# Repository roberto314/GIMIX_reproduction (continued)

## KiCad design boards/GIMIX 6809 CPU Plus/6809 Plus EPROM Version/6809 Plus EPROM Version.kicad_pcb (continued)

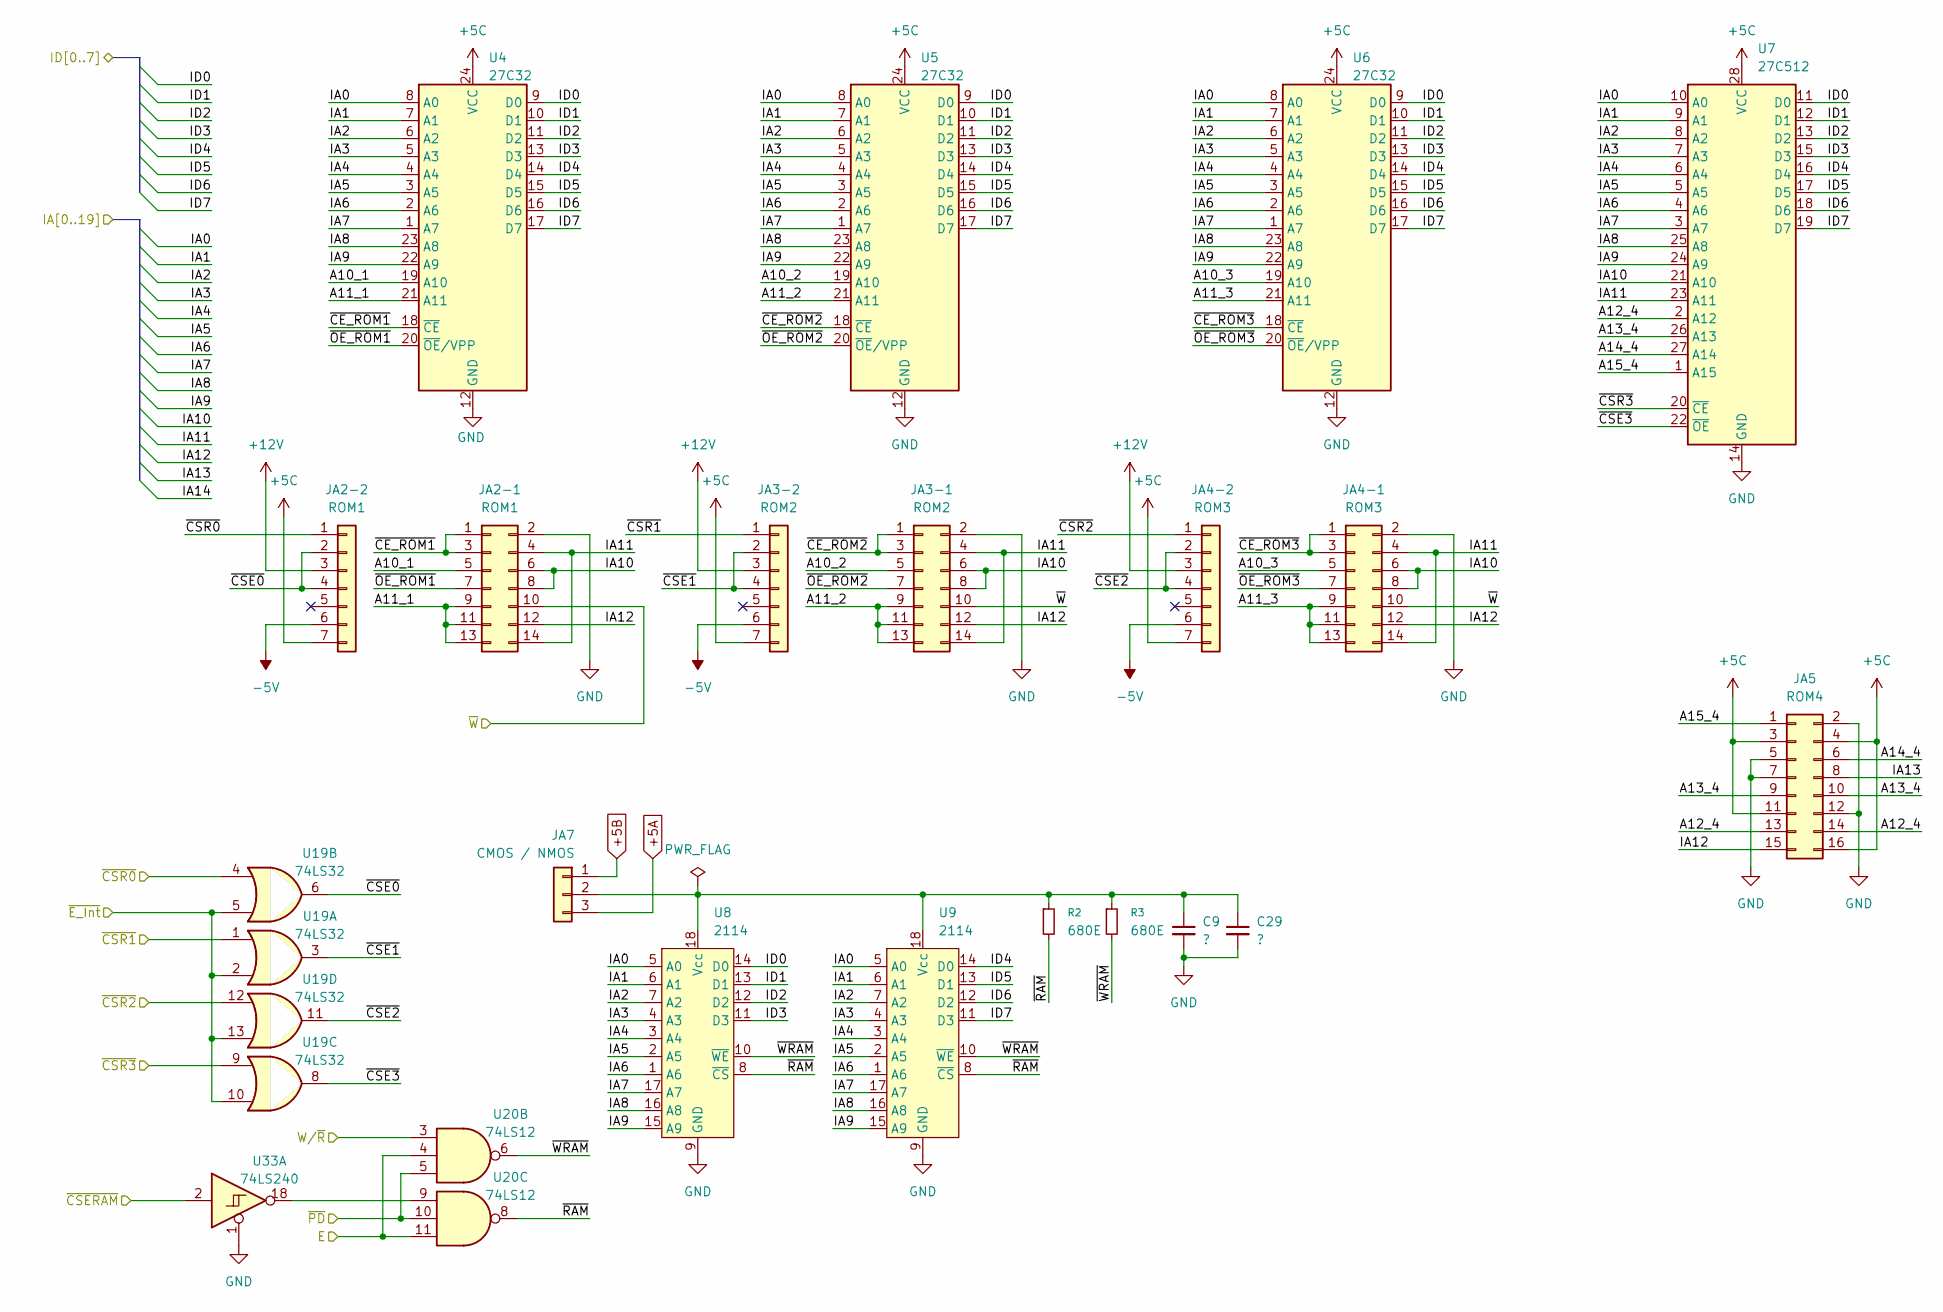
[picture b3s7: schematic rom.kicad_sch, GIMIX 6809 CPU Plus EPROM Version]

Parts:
C9, C29: ?; C_Disc_D3.8mm_W2.6mm_P2.50mm
JA2-1: ROM1; PinHeader_2x07_P2.54mm_Vertical
JA2-2: ROM1; PinHeader_1x07_P2.54mm_Vertical
JA3-1: ROM2; PinHeader_2x07_P2.54mm_Vertical
JA3-2: ROM2; PinHeader_1x07_P2.54mm_Vertical
JA4-1: ROM3; PinHeader_2x07_P2.54mm_Vertical
JA4-2: ROM3; PinHeader_1x07_P2.54mm_Vertical
JA5: ROM4; PinHeader_2x08_P2.54mm_Vertical
JA7: CMOS / NMOS; PinHeader_1x03_P2.54mm_Vertical
R2, R3: 680E; R_Axial_DIN0207_L6.3mm_D2.5mm_P10.16mm_Horizontal
U4, U5, U6: 27C32; DIP-24_W15.24mm
U7: 27C512; DIP-28_W15.24mm
U8, U9: 2114; DIP-18_W7.62mm
U19: 74LS32; DIP-14_W7.62mm
U20: 74LS12; DIP-14_W7.62mm
U33: 74LS240; DIP-20_W7.62mm

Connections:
+5A: JA7.3; also elsewhere on the board
+5B: JA7.1; also elsewhere on the board
+5C: JA2-2.7, JA3-2.7, JA4-2.7, JA5.3, JA5.4, JA5.11, JA5.16, U4.24 (VCC), U5.24 (VCC), U6.24 (VCC), U7.28 (VCC); also elsewhere on the board
+12V: JA2-2.3, JA3-2.3, JA4-2.3; also elsewhere on the board
-5V: JA2-2.6, JA3-2.6, JA4-2.6; also elsewhere on the board
/E: U20.4, U20.11; also elsewhere on the board
/IA0: U4.8 (A0), U5.8 (A0), U6.8 (A0), U7.10 (A0), U8.5 (A0), U9.5 (A0); also elsewhere on the board
/IA1: U4.7 (A1), U5.7 (A1), U6.7 (A1), U7.9 (A1), U8.6 (A1), U9.6 (A1); also elsewhere on the board
/IA2: U4.6 (A2), U5.6 (A2), U6.6 (A2), U7.8 (A2), U8.7 (A2), U9.7 (A2); also elsewhere on the board
/IA3: U4.5 (A3), U5.5 (A3), U6.5 (A3), U7.7 (A3), U8.4 (A3), U9.4 (A3); also elsewhere on the board
/IA4: U4.4 (A4), U5.4 (A4), U6.4 (A4), U7.6 (A4), U8.3 (A4), U9.3 (A4); also elsewhere on the board
/IA5: U4.3 (A5), U5.3 (A5), U6.3 (A5), U7.5 (A5), U8.2 (A5), U9.2 (A5); also elsewhere on the board
/IA6: U4.2 (A6), U5.2 (A6), U6.2 (A6), U7.4 (A6), U8.1 (A6), U9.1 (A6); also elsewhere on the board
/IA7: U4.1 (A7), U5.1 (A7), U6.1 (A7), U7.3 (A7), U8.17 (A7), U9.17 (A7); also elsewhere on the board
/IA8: U4.23 (A8), U5.23 (A8), U6.23 (A8), U7.25 (A8), U8.16 (A8), U9.16 (A8); also elsewhere on the board
/IA9: U4.22 (A9), U5.22 (A9), U6.22 (A9), U7.24 (A9), U8.15 (A9), U9.15 (A9); also elsewhere on the board
/IA10: JA2-1.6, JA2-1.8, JA3-1.6, JA3-1.8, JA4-1.6, JA4-1.8, U7.21 (A10); also elsewhere on the board
/IA11: JA2-1.4, JA2-1.14, JA3-1.4, JA3-1.14, JA4-1.4, JA4-1.14, U7.23 (A11); also elsewhere on the board
/IA12: JA2-1.12, JA3-1.12, JA4-1.12, JA5.15; also elsewhere on the board
/IA13: JA5.8; also elsewhere on the board
/ID0: U4.9 (D0), U5.9 (D0), U6.9 (D0), U7.11 (D0), U8.14 (D0); also elsewhere on the board
/ID1: U4.10 (D1), U5.10 (D1), U6.10 (D1), U7.12 (D1), U8.13 (D1); also elsewhere on the board
/ID2: U4.11 (D2), U5.11 (D2), U6.11 (D2), U7.13 (D2), U8.12 (D2); also elsewhere on the board
/ID3: U4.13 (D3), U5.13 (D3), U6.13 (D3), U7.15 (D3), U8.11 (D3); also elsewhere on the board
/ID4: U4.14 (D4), U5.14 (D4), U6.14 (D4), U7.16 (D4), U9.14 (D0); also elsewhere on the board
/ID5: U4.15 (D5), U5.15 (D5), U6.15 (D5), U7.17 (D5), U9.13 (D1); also elsewhere on the board
/ID6: U4.16 (D6), U5.16 (D6), U6.16 (D6), U7.18 (D6), U9.12 (D2); also elsewhere on the board
/ID7: U4.17 (D7), U5.17 (D7), U6.17 (D7), U7.19 (D7), U9.11 (D3); also elsewhere on the board
/ROM/A10_1: JA2-1.5, U4.19 (A10)
/ROM/A10_2: JA3-1.5, U5.19 (A10)
/ROM/A10_3: JA4-1.5, U6.19 (A10)
/ROM/A11_1: JA2-1.9, JA2-1.11, JA2-1.13, U4.21 (A11)
/ROM/A11_2: JA3-1.9, JA3-1.11, JA3-1.13, U5.21 (A11)
/ROM/A11_3: JA4-1.9, JA4-1.11, JA4-1.13, U6.21 (A11)
/ROM/A12_4: JA5.13, JA5.14, U7.2 (A12)
/ROM/A13_4: JA5.9, JA5.10, U7.26 (A13)
/ROM/A14_4: JA5.6, U7.27 (A14)
/ROM/A15_4: JA5.1, U7.1 (A15)
/ROM/~CE_ROM1: JA2-1.1, JA2-1.3, U4.18 (~CE)
/ROM/~CE_ROM2: JA3-1.1, JA3-1.3, U5.18 (~CE)
/ROM/~CE_ROM3: JA4-1.1, JA4-1.3, U6.18 (~CE)
/ROM/~CSE0: JA2-2.2, JA2-2.4, U19.6
/ROM/~CSE1: JA3-2.2, JA3-2.4, U19.3
/ROM/~CSE2: JA4-2.2, JA4-2.4, U19.11
/ROM/~CSE3: U7.22 (~OE), U19.8
/ROM/~OE_ROM1: JA2-1.7, U4.20 (~OE/VPP)
/ROM/~OE_ROM2: JA3-1.7, U5.20 (~OE/VPP)
/ROM/~OE_ROM3: JA4-1.7, U6.20 (~OE/VPP)
/ROM/~RAM: R2.2, U8.8 (~CS), U9.8 (~CS), U20.8
/ROM/~WRAM: R3.2, U8.10 (~WE), U9.10 (~WE), U20.6
/W/~R: U20.3; also elsewhere on the board
/~CSERAM: U33.2; also elsewhere on the board
/~CSR0: JA2-2.1, U19.4; also elsewhere on the board
/~CSR1: JA3-2.1, U19.1; also elsewhere on the board
/~CSR2: JA4-2.1, U19.12; also elsewhere on the board
/~CSR3: U7.20 (~CE), U19.9; also elsewhere on the board
/~E_Int: U19.2, U19.5, U19.10, U19.13; also elsewhere on the board
/~PD: U20.5, U20.10; also elsewhere on the board
/~W: JA2-1.10, JA3-1.10, JA4-1.10; also elsewhere on the board
GND: C9.2, C29.2, JA2-1.2, JA3-1.2, JA4-1.2, JA5.2, JA5.5, JA5.7, JA5.12, U4.12 (GND), U5.12 (GND), U6.12 (GND), U7.14 (GND), U8.9 (GND), U9.9 (GND), U33.1; also elsewhere on the board
unnamed: C9.1, C29.1, JA7.2, R2.1, R3.1, U8.18 (Vcc), U9.18 (Vcc)
unnamed: U20.9, U33.18

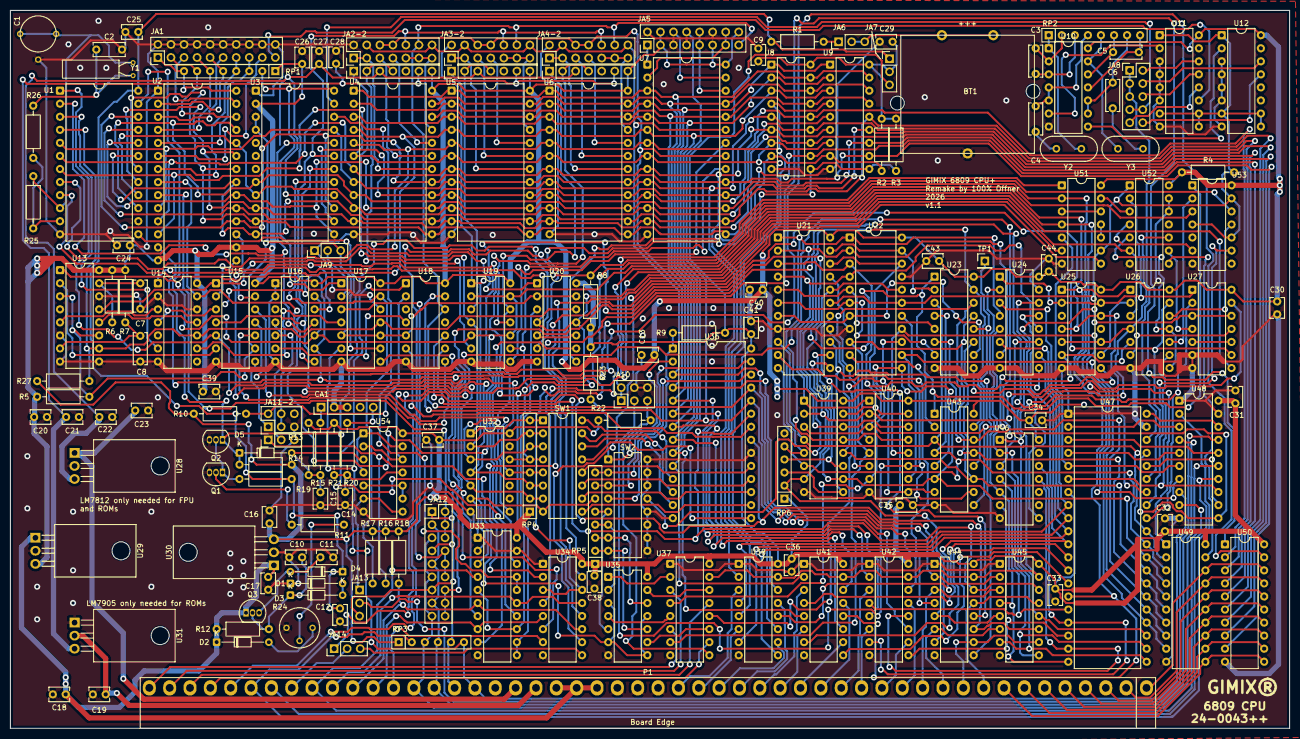
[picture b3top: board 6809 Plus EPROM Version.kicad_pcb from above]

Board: 2 copper layers, 248.9 x 139.7 mm, 167 parts (0 on the bottom side), 294 nets.

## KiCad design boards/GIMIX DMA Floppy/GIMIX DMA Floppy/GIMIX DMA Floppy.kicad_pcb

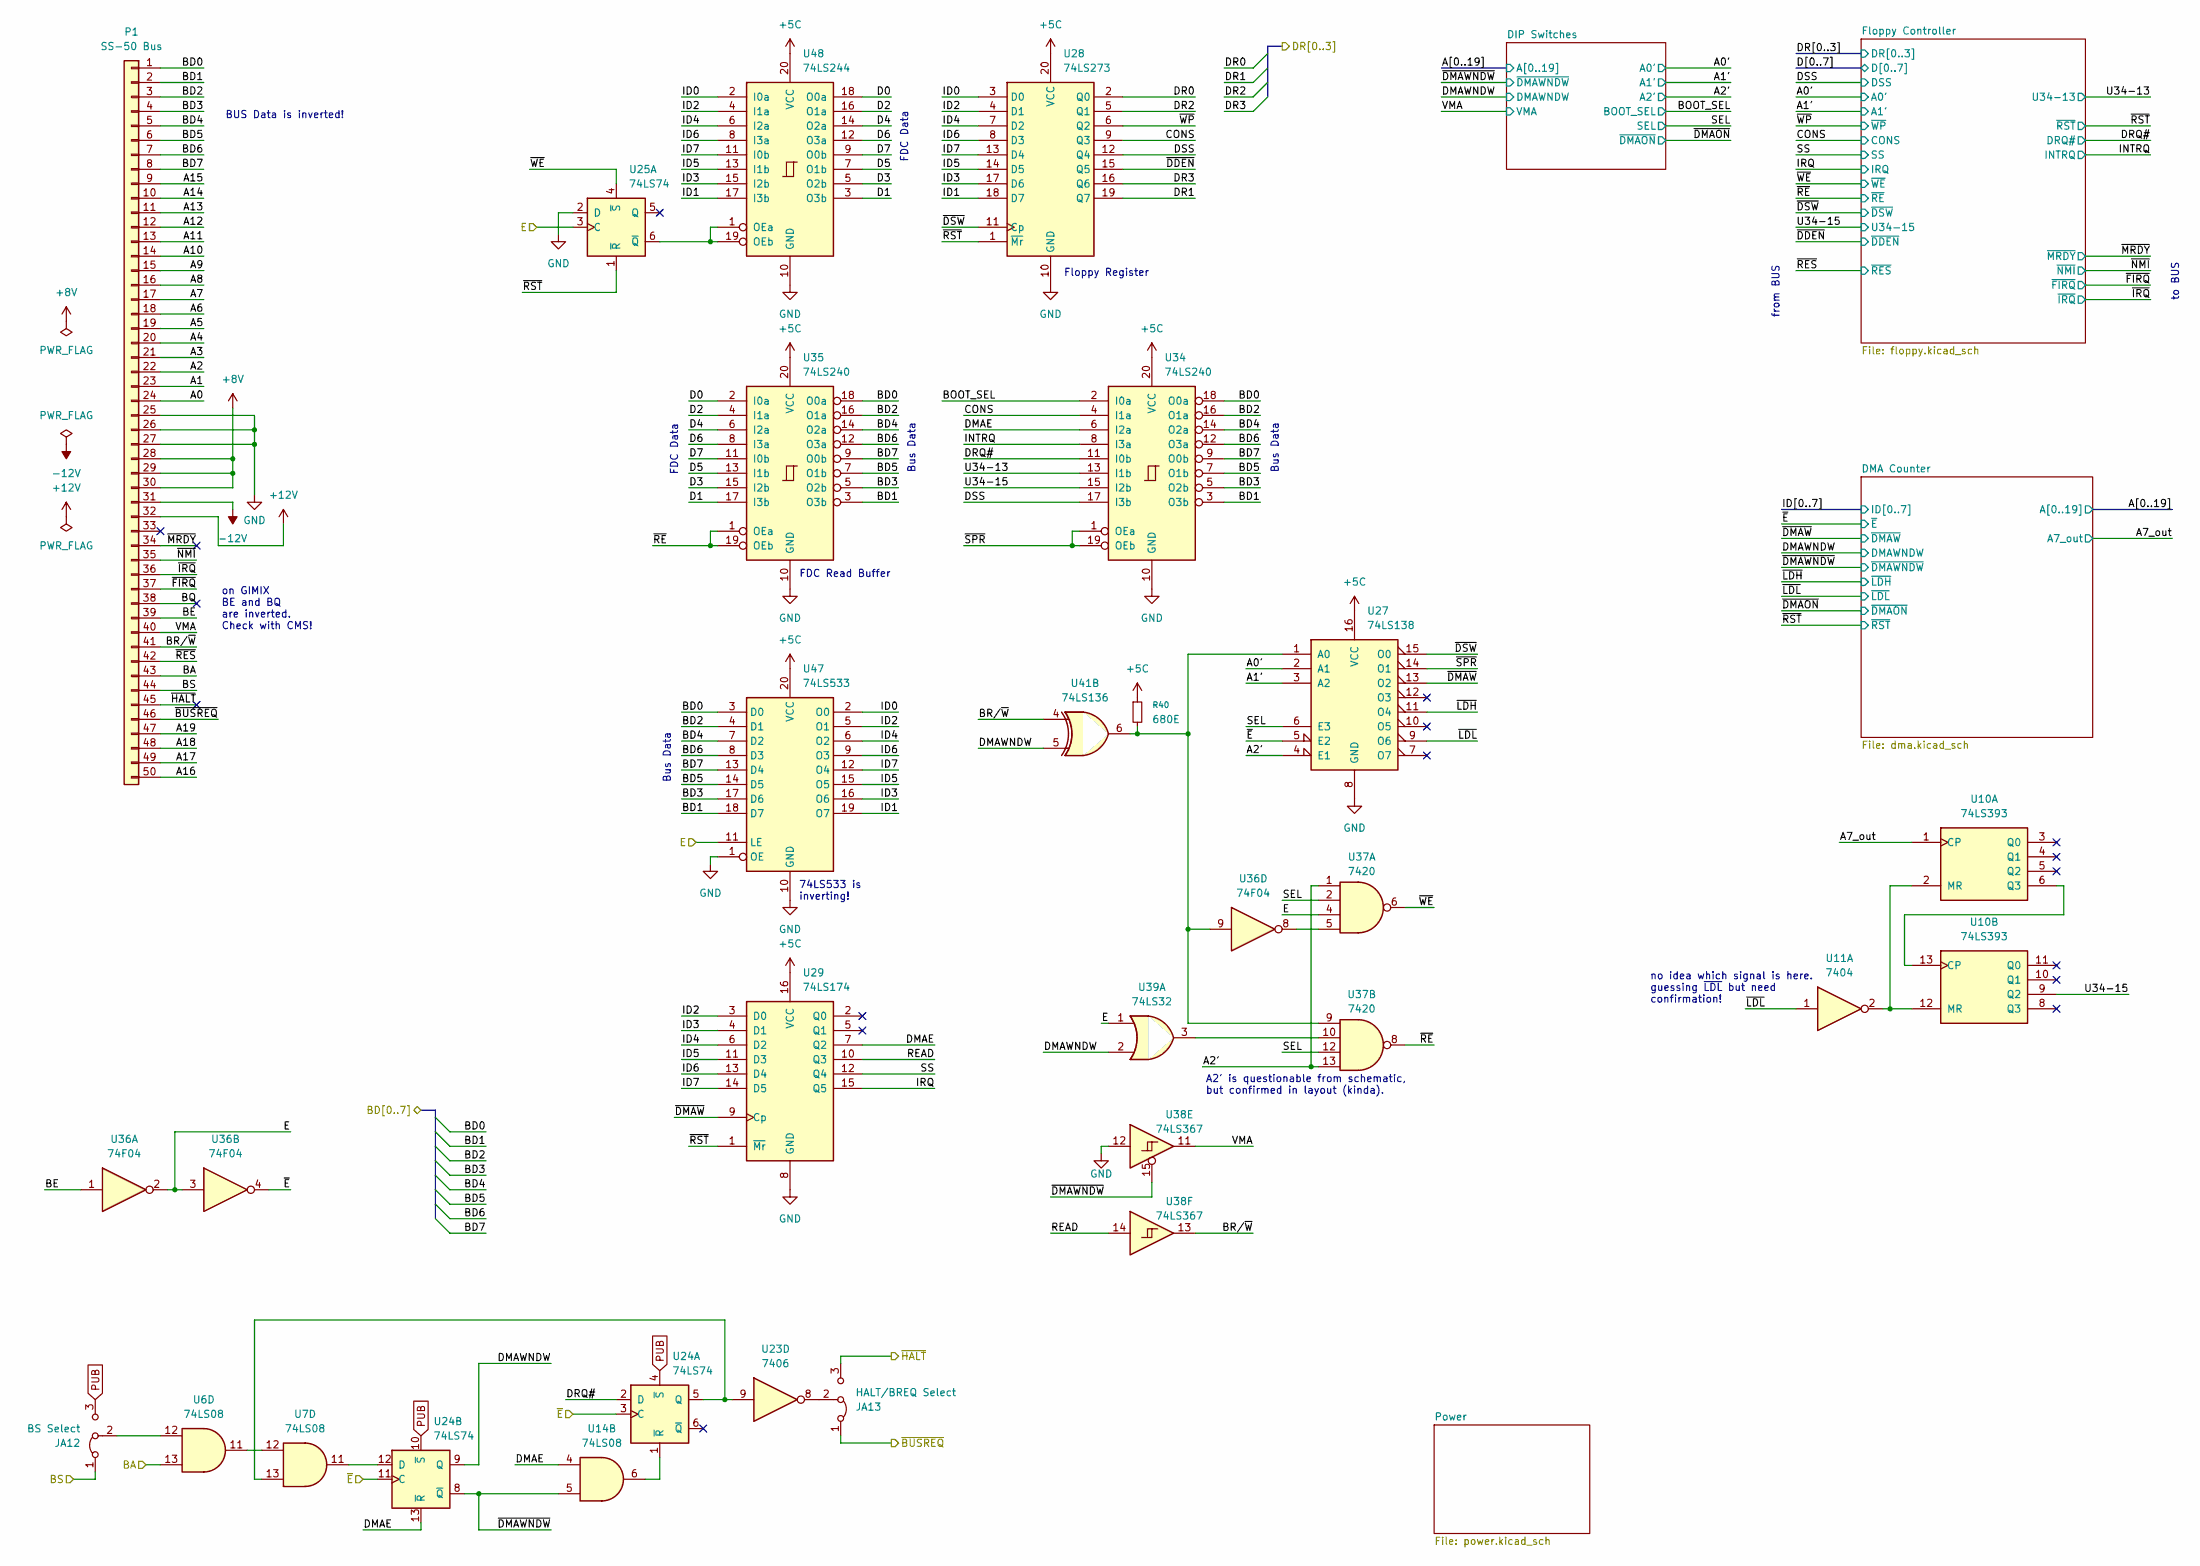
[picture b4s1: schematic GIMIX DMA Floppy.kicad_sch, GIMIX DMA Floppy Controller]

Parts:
JA12: BS Select; PinHeader_1x03_P2.54mm_Vertical
JA13: HALT/BREQ Select; PinHeader_1x03_P2.54mm_Vertical
P1: SS-50 Bus; SS-50_new
R40: 680E; R_Axial_DIN0207_L6.3mm_D2.5mm_P10.16mm_Horizontal
U6, U7, U14: 74LS08; DIP-14_W7.62mm
U10: 74LS393; DIP-14_W7.62mm
U11: 7404; DIP-14_W7.62mm
U23: 7406; DIP-14_W7.62mm
U24, U25: 74LS74; DIP-14_W7.62mm
U27: 74LS138; DIP-16_W7.62mm
U28: 74LS273; DIP-20_W7.62mm
U29: 74LS174; DIP-16_W7.62mm
U34, U35: 74LS240; DIP-20_W7.62mm
U36: 74F04; DIP-14_W7.62mm
U37: 7420; DIP-14_W7.62mm
U38: 74LS367; DIP-16_W7.62mm
U39: 74LS32; DIP-14_W7.62mm
U41: 74LS136; DIP-14_W7.62mm
U47: 74LS533; DIP-20_W7.62mm
U48: 74LS244; DIP-20_W7.62mm

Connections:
+5C: R40.1, U27.16 (VCC), U28.20 (VCC), U29.16 (VCC), U34.20 (VCC), U35.20 (VCC), U47.20 (VCC), U48.20 (VCC); also elsewhere on the board
+8V: P1.28, P1.29, P1.30; also elsewhere on the board
+12V: P1.32
-12V: P1.31
/A0: P1.24; also elsewhere on the board
/A0': U27.2 (A1); also elsewhere on the board
/A1: P1.23; also elsewhere on the board
/A1': U27.3 (A2); also elsewhere on the board
/A2: P1.22; also elsewhere on the board
/A2': U27.4 (E1), U37.1, U37.13; also elsewhere on the board
/A3: P1.21; also elsewhere on the board
/A4: P1.20; also elsewhere on the board
/A5: P1.19; also elsewhere on the board
/A6: P1.18; also elsewhere on the board
/A7: P1.17; also elsewhere on the board
/A7_out: U10.1 (CP); also elsewhere on the board
/A8: P1.16; also elsewhere on the board
/A9: P1.15; also elsewhere on the board
/A10: P1.14; also elsewhere on the board
/A11: P1.13; also elsewhere on the board
/A12: P1.12; also elsewhere on the board
/A13: P1.11; also elsewhere on the board
/A14: P1.10; also elsewhere on the board
/A15: P1.9; also elsewhere on the board
/A16: P1.50; also elsewhere on the board
/A17: P1.49; also elsewhere on the board
/A18: P1.48; also elsewhere on the board
/A19: P1.47; also elsewhere on the board
/BA: P1.43, U6.13
/BD0: P1.1, U34.18 (O0a), U35.18 (O0a), U47.3 (D0)
/BD1: P1.2, U34.3 (O3b), U35.3 (O3b), U47.18 (D7)
/BD2: P1.3, U34.16 (O1a), U35.16 (O1a), U47.4 (D1)
/BD3: P1.4, U34.5 (O2b), U35.5 (O2b), U47.17 (D6)
/BD4: P1.5, U34.14 (O2a), U35.14 (O2a), U47.7 (D2)
/BD5: P1.6, U34.7 (O1b), U35.7 (O1b), U47.14 (D5)
/BD6: P1.7, U34.12 (O3a), U35.12 (O3a), U47.8 (D3)
/BD7: P1.8, U34.9 (O0b), U35.9 (O0b), U47.13 (D4)
/BE: P1.39, U36.1
/BOOT_SEL: U34.2 (I0a); also elsewhere on the board
/BQ: P1.38
/BR/~W: P1.41, U38.13, U41.4
/BS: JA12.1 (A), P1.44
/CONS: U28.9 (Q3), U34.4 (I1a); also elsewhere on the board
/D0: U35.2 (I0a), U48.18 (O0a); also elsewhere on the board
/D1: U35.17 (I3b), U48.3 (O3b); also elsewhere on the board
/D2: U35.4 (I1a), U48.16 (O1a); also elsewhere on the board
/D3: U35.15 (I2b), U48.5 (O2b); also elsewhere on the board
/D4: U35.6 (I2a), U48.14 (O2a); also elsewhere on the board
/D5: U35.13 (I1b), U48.7 (O1b); also elsewhere on the board
/D6: U35.8 (I3a), U48.12 (O3a); also elsewhere on the board
/D7: U35.11 (I0b), U48.9 (O0b); also elsewhere on the board
/DMAE: U14.4, U24.13 (~R), U29.7 (Q2), U34.6 (I2a)
/DMAWNDW: U24.9 (Q), U39.2, U41.5; also elsewhere on the board
/DR0: U28.2 (Q0); also elsewhere on the board
/DR1: U28.19 (Q7); also elsewhere on the board
/DR2: U28.5 (Q1); also elsewhere on the board
/DR3: U28.16 (Q6); also elsewhere on the board
/DRQ#: U24.2 (D), U34.11 (I0b); also elsewhere on the board
/DSS: U28.12 (Q4), U34.17 (I3b); also elsewhere on the board
/E: U25.3 (C), U36.2, U36.3, U37.4, U39.1, U47.11 (LE)
/ID0: U28.3 (D0), U47.2 (O0), U48.2 (I0a); also elsewhere on the board
/ID1: U28.18 (D7), U47.19 (O7), U48.17 (I3b); also elsewhere on the board
/ID2: U28.4 (D1), U29.3 (D0), U47.5 (O1), U48.4 (I1a); also elsewhere on the board
/ID3: U28.17 (D6), U29.4 (D1), U47.16 (O6), U48.15 (I2b); also elsewhere on the board
/ID4: U28.7 (D2), U29.6 (D2), U47.6 (O2), U48.6 (I2a); also elsewhere on the board
/ID5: U28.14 (D5), U29.11 (D3), U47.15 (O5), U48.13 (I1b); also elsewhere on the board
/ID6: U28.8 (D3), U29.13 (D4), U47.9 (O3), U48.8 (I3a); also elsewhere on the board
/ID7: U28.13 (D4), U29.14 (D5), U47.12 (O4), U48.11 (I0b); also elsewhere on the board
/INTRQ: U34.8 (I3a); also elsewhere on the board
/IRQ: U29.15 (Q5); also elsewhere on the board
/READ: U29.10 (Q3), U38.14
/SEL: U27.6 (E3), U37.2, U37.12; also elsewhere on the board
/SS: U29.12 (Q4); also elsewhere on the board
/U34-13: U34.13 (I1b); also elsewhere on the board
/U34-15: U10.9 (Q2), U34.15 (I2b); also elsewhere on the board
/VMA: P1.40, U38.11; also elsewhere on the board
/~BUSREQ: JA13.1 (A), P1.46
/~DDEN: U28.15 (Q5); also elsewhere on the board
/~DMAWNDW: U14.5, U24.8 (~Q), U38.15; also elsewhere on the board
/~DMAW: U27.13 (O2), U29.9 (Cp); also elsewhere on the board
/~DSW: U27.15 (O0), U28.11 (Cp); also elsewhere on the board
/~E: U24.3 (C), U24.11 (C), U27.5 (E2), U36.4; also elsewhere on the board
/~FIRQ: P1.37; also elsewhere on the board
/~HALT: JA13.3 (B), P1.45
/~IRQ: P1.36; also elsewhere on the board
/~LDH: U27.11 (O4); also elsewhere on the board
/~LDL: U11.1, U27.9 (O6); also elsewhere on the board
/~MRDY: P1.34; also elsewhere on the board
/~NMI: P1.35; also elsewhere on the board
/~RES: P1.42; also elsewhere on the board
/~RE: U35.1 (OEa), U35.19 (OEb), U37.8; also elsewhere on the board
/~RST: U25.1 (~R), U28.1 (~Mr), U29.1 (~Mr); also elsewhere on the board
/~SPR: U27.14 (O1), U34.1 (OEa), U34.19 (OEb)
/~WE: U25.4 (~S), U37.6; also elsewhere on the board
/~WP: U28.6 (Q2); also elsewhere on the board
GND: P1.25, P1.26, P1.27, U25.2 (D), U27.8 (GND), U28.10 (GND), U29.8 (GND), U34.10 (GND), U35.10 (GND), U38.12, U47.1 (OE), U47.10 (GND), U48.10 (GND); also elsewhere on the board
unnamed: JA12.2 (C), U6.12
unnamed: JA13.2 (C), U23.8
unnamed: U6.11, U7.12
unnamed: U10.2 (MR), U10.12 (MR), U11.2
unnamed: U10.6 (Q3), U10.13 (CP)
unnamed: U7.13, U23.9, U24.5 (Q)
unnamed: U14.6, U24.1 (~R)
unnamed: U7.11, U24.12 (D)
unnamed: U25.6 (~Q), U48.1 (OEa), U48.19 (OEb)
unnamed: R40.2, U27.1 (A0), U36.9, U37.9, U41.6
unnamed: U36.8, U37.5
unnamed: U37.10, U39.3
PUB: JA12.3 (B), U24.4 (~S), U24.10 (~S); also elsewhere on the board

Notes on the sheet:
74LS533 is inverting!
Floppy Register
Bus Data
A2' is questionable from schematic, but confirmed in layout (kinda).
on GIMIX BE and BQ are inverted. Check with CMS!
no idea which signal is here. guessing ~{LDL} but need confirmation!
FDC Data
BUS Data is inverted!
FDC Read Buffer
from BUS
to BUS

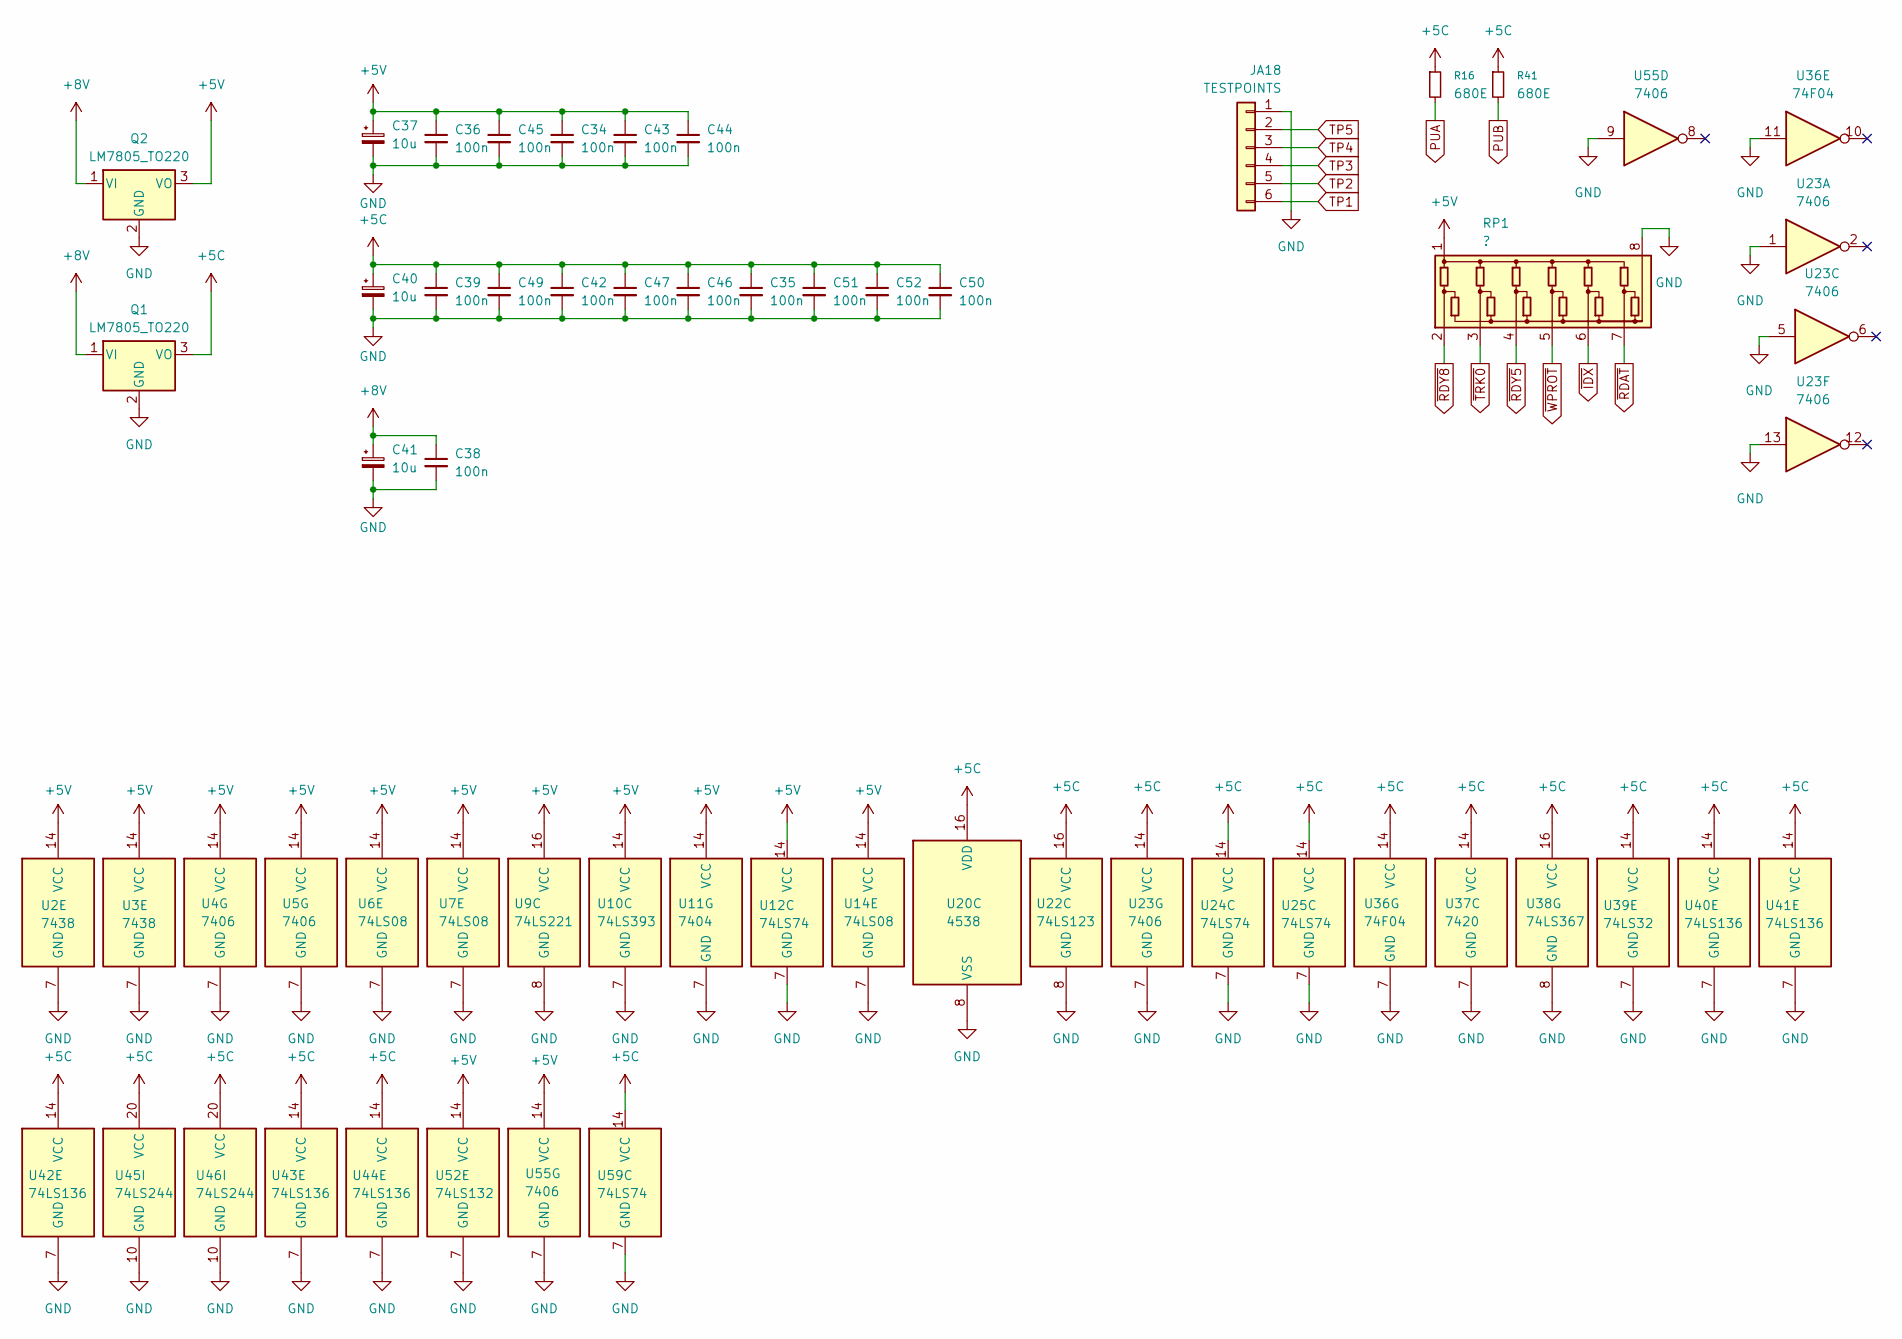
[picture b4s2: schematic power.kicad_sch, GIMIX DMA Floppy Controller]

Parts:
C34, C35, C36, C38, C39, C42, C43, C44, C45, C46, C47, C49, C50, C51, C52: 100n; C_Disc_D3.0mm_W1.6mm_P2.50mm
C37, C40: 10u; CP_Radial_D5.0mm_P2.50mm
C41: 10u; CP_Radial_D12.5mm_P5.00mm
JA18: TESTPOINTS; PinHeader_1x06_P2.54mm_Vertical
Q1, Q2: LM7805_TO220; TO-220F-3_Horizontal_TabDown
R16, R41: 680E; R_Axial_DIN0207_L6.3mm_D2.5mm_P10.16mm_Horizontal
RP1: ?; R_Array_SIP8
U2, U3: 7438; DIP-14_W7.62mm
U4, U5, U23, U55: 7406; DIP-14_W7.62mm
U6, U7, U14: 74LS08; DIP-14_W7.62mm
U9: 74LS221; DIP-16_W7.62mm
U10: 74LS393; DIP-14_W7.62mm
U11: 7404; DIP-14_W7.62mm
U12, U24, U25, U59: 74LS74; DIP-14_W7.62mm
U20: 4538; DIP-16_W7.62mm
U22: 74LS123; DIP-16_W7.62mm
U36: 74F04; DIP-14_W7.62mm
U37: 7420; DIP-14_W7.62mm
U38: 74LS367; DIP-16_W7.62mm
U39: 74LS32; DIP-14_W7.62mm
U40, U41, U42, U43, U44: 74LS136; DIP-14_W7.62mm
U45, U46: 74LS244; DIP-20_W7.62mm
U52: 74LS132; DIP-14_W7.62mm

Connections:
+5C: C35.1, C39.1, C40.1, C42.1, C46.1, C47.1, C49.1, C50.1, C51.1, C52.1, Q1.3 (VO), R16.1, R41.1, U20.16 (VDD), U22.16 (VCC), U23.14 (VCC), U24.14 (VCC), U25.14 (VCC), U36.14 (VCC), U37.14 (VCC), U38.16 (VCC), U39.14 (VCC), U40.14 (VCC), U41.14 (VCC), U42.14 (VCC), U43.14 (VCC), U44.14 (VCC), U45.20 (VCC), U46.20 (VCC), U59.14 (VCC); also elsewhere on the board
+5V: C34.1, C36.1, C37.1, C43.1, C44.1, C45.1, Q2.3 (VO), RP1.1 (COM1), U2.14 (VCC), U3.14 (VCC), U4.14 (VCC), U5.14 (VCC), U6.14 (VCC), U7.14 (VCC), U9.16 (VCC), U10.14 (VCC), U11.14 (VCC), U12.14 (VCC), U14.14 (VCC), U52.14 (VCC), U55.14 (VCC); also elsewhere on the board
+8V: C38.1, C41.1, Q1.1 (VI), Q2.1 (VI); also elsewhere on the board
GND: C34.2, C35.2, C36.2, C37.2, C38.2, C39.2, C40.2, C41.2, C42.2, C43.2, C44.2, C45.2, C46.2, C47.2, C49.2, C50.2, C51.2, C52.2, JA18.1, Q1.2 (GND), Q2.2 (GND), RP1.8 (COM2), U2.7 (GND), U3.7 (GND), U4.7 (GND), U5.7 (GND), U6.7 (GND), U7.7 (GND), U9.8 (GND), U10.7 (GND), U11.7 (GND), U12.7 (GND), U14.7 (GND), U20.8 (VSS), U22.8 (GND), U23.1, U23.5, U23.7 (GND), U23.13, U24.7 (GND), U25.7 (GND), U36.7 (GND), U36.11, U37.7 (GND), U38.8 (GND), U39.7 (GND), U40.7 (GND), U41.7 (GND), U42.7 (GND), U43.7 (GND), U44.7 (GND), U45.10 (GND), U46.10 (GND), U52.7 (GND), U55.7 (GND), U55.9, U59.7 (GND); also elsewhere on the board
PUA: R16.2; also elsewhere on the board
PUB: R41.2; also elsewhere on the board
TP1: JA18.6; also elsewhere on the board
TP2: JA18.5; also elsewhere on the board
TP3: JA18.4; also elsewhere on the board
TP4: JA18.3; also elsewhere on the board
TP5: JA18.2; also elsewhere on the board
~IDX: RP1.6 (R5); also elsewhere on the board
~RDAT: RP1.7 (R6); also elsewhere on the board
~RDY5: RP1.4 (R3); also elsewhere on the board
~RDY8: RP1.2 (R1); also elsewhere on the board
~TRK0: RP1.3 (R2); also elsewhere on the board
~WPROT: RP1.5 (R4); also elsewhere on the board
